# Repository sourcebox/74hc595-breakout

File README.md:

# About

KiCad project files of a breakout board containing 8 cascaded 74HC595
shift registers offering serial-in/parallel-out functionality.

This board is intended as microcontroller GPIO extension for prototyping purposes.

# License

CC-BY-4.0

By: Oliver Rockstedt <info@sourcebox.de>

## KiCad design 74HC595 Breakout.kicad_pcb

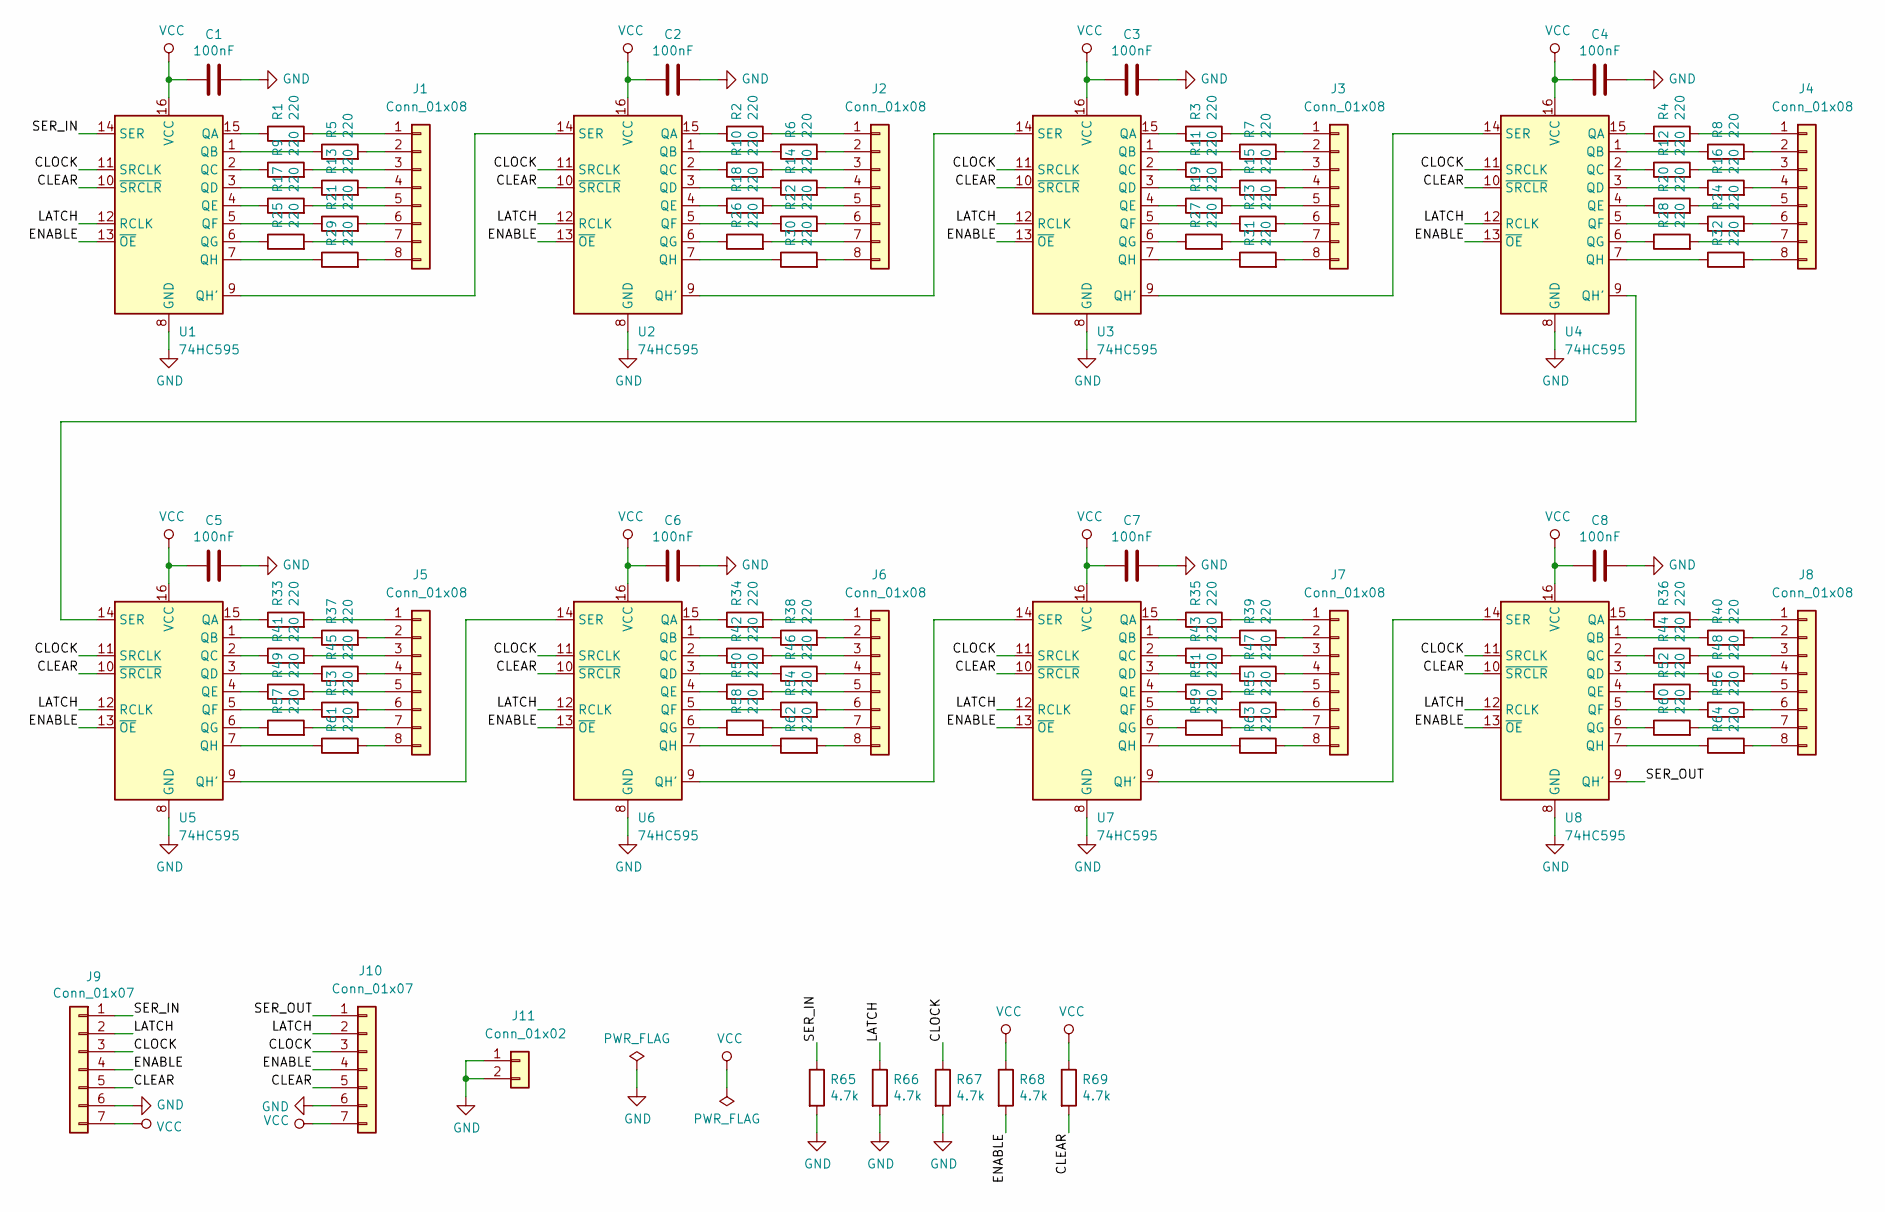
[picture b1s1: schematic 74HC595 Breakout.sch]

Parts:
C1, C2, C3, C4, C5, C6, C7, C8: 100nF; C_0805_2012Metric
J1, J2, J3, J4, J5, J6, J7, J8: Conn_01x08; PinHeader_1x08_P2.54mm_Vertical
J9, J10: Conn_01x07; PinHeader_1x07_P2.54mm_Vertical
J11: Conn_01x02; PinHeader_1x02_P2.54mm_Vertical
R1, R2, R3, R4, R5, R6, R7, R8, R9, R10, R11, R12, R13, R14, R15, R16, R17, R18, R19, R20, R21, R22, R23, R24, R25, R26, R27, R28, R29, R30, R31, R32, R33, R34, R35, R36, R37, R38, R39, R40, R41, R42, R43, R44, R45, R46, R47, R48, R49, R50, R51, R52, R53, R54, R55, R56, R57, R58, R59, R60, R61, R62, R63, R64: 220; R_0805_2012Metric
R65, R66, R67, R68, R69: 4.7k; R_0805_2012Metric
U1, U2, U3, U4, U5, U6, U7, U8: 74HC595; SOIC-16_3.9x9.9mm_P1.27mm

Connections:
/CLEAR: J9.5, J10.5, R69.2, U1.10 (~SRCLR), U2.10 (~SRCLR), U3.10 (~SRCLR), U4.10 (~SRCLR), U5.10 (~SRCLR), U6.10 (~SRCLR), U7.10 (~SRCLR), U8.10 (~SRCLR)
/CLOCK: J9.3, J10.3, R67.1, U1.11 (SRCLK), U2.11 (SRCLK), U3.11 (SRCLK), U4.11 (SRCLK), U5.11 (SRCLK), U6.11 (SRCLK), U7.11 (SRCLK), U8.11 (SRCLK)
/ENABLE: J9.4, J10.4, R68.2, U1.13 (~OE), U2.13 (~OE), U3.13 (~OE), U4.13 (~OE), U5.13 (~OE), U6.13 (~OE), U7.13 (~OE), U8.13 (~OE)
/LATCH: J9.2, J10.2, R66.1, U1.12 (RCLK), U2.12 (RCLK), U3.12 (RCLK), U4.12 (RCLK), U5.12 (RCLK), U6.12 (RCLK), U7.12 (RCLK), U8.12 (RCLK)
/SER_IN: J9.1, R65.1, U1.14 (SER)
/SER_OUT: J10.1, U8.9 (QH')
GND: C1.1, C2.1, C3.1, C4.1, C5.1, C6.1, C7.1, C8.1, J9.6, J10.6, J11.1, J11.2, R65.2, R66.2, R67.2, U1.8 (GND), U2.8 (GND), U3.8 (GND), U4.8 (GND), U5.8 (GND), U6.8 (GND), U7.8 (GND), U8.8 (GND)
unnamed: J1.1, R1.2
unnamed: J1.2, R5.2
unnamed: J1.3, R9.2
unnamed: J1.4, R13.2
unnamed: J1.5, R17.2
unnamed: J1.6, R21.2
unnamed: J1.7, R25.2
unnamed: J1.8, R29.2
unnamed: J2.1, R2.2
unnamed: J2.2, R6.2
unnamed: J2.3, R10.2
unnamed: J2.4, R14.2
unnamed: J2.5, R18.2
unnamed: J2.6, R22.2
unnamed: J2.7, R26.2
unnamed: J2.8, R30.2
unnamed: J3.1, R3.2
unnamed: J3.2, R7.2
unnamed: J3.3, R11.2
unnamed: J3.4, R15.2
unnamed: J3.5, R19.2
unnamed: J3.6, R23.2
unnamed: J3.7, R27.2
unnamed: J3.8, R31.2
unnamed: J4.1, R4.2
unnamed: J4.2, R8.2
unnamed: J4.3, R12.2
unnamed: J4.4, R16.2
unnamed: J4.5, R20.2
unnamed: J4.6, R24.2
unnamed: J4.7, R28.2
unnamed: J4.8, R32.2
unnamed: J5.1, R33.2
unnamed: J5.2, R37.2
unnamed: J5.3, R41.2
unnamed: J5.4, R45.2
unnamed: J5.5, R49.2
unnamed: J5.6, R53.2
unnamed: J5.7, R57.2
unnamed: J5.8, R61.2
unnamed: J6.1, R34.2
unnamed: J6.2, R38.2
unnamed: J6.3, R42.2
unnamed: J6.4, R46.2
unnamed: J6.5, R50.2
unnamed: J6.6, R54.2
unnamed: J6.7, R58.2
unnamed: J6.8, R62.2
unnamed: J7.1, R35.2
unnamed: J7.2, R39.2
unnamed: J7.3, R43.2
unnamed: J7.4, R47.2
unnamed: J7.5, R51.2
unnamed: J7.6, R55.2
unnamed: J7.7, R59.2
unnamed: J7.8, R63.2
unnamed: J8.1, R36.2
unnamed: J8.2, R40.2
unnamed: J8.3, R44.2
unnamed: J8.4, R48.2
unnamed: J8.5, R52.2
unnamed: J8.6, R56.2
unnamed: J8.7, R60.2
unnamed: J8.8, R64.2
unnamed: R1.1, U1.15 (QA)
unnamed: R2.1, U2.15 (QA)
unnamed: R3.1, U3.15 (QA)
unnamed: R4.1, U4.15 (QA)
unnamed: R5.1, U1.1 (QB)
unnamed: R6.1, U2.1 (QB)
unnamed: R7.1, U3.1 (QB)
unnamed: R8.1, U4.1 (QB)
unnamed: R9.1, U1.2 (QC)
unnamed: R10.1, U2.2 (QC)
unnamed: R11.1, U3.2 (QC)
unnamed: R12.1, U4.2 (QC)
unnamed: R13.1, U1.3 (QD)
unnamed: R14.1, U2.3 (QD)
unnamed: R15.1, U3.3 (QD)
unnamed: R16.1, U4.3 (QD)
unnamed: R17.1, U1.4 (QE)
unnamed: R18.1, U2.4 (QE)
unnamed: R19.1, U3.4 (QE)
unnamed: R20.1, U4.4 (QE)
unnamed: R21.1, U1.5 (QF)
unnamed: R22.1, U2.5 (QF)
unnamed: R23.1, U3.5 (QF)
unnamed: R24.1, U4.5 (QF)
unnamed: R25.1, U1.6 (QG)
unnamed: R26.1, U2.6 (QG)
unnamed: R27.1, U3.6 (QG)
unnamed: R28.1, U4.6 (QG)
unnamed: R29.1, U1.7 (QH)
unnamed: R30.1, U2.7 (QH)
unnamed: R31.1, U3.7 (QH)
unnamed: R32.1, U4.7 (QH)
unnamed: R33.1, U5.15 (QA)
unnamed: R34.1, U6.15 (QA)
unnamed: R35.1, U7.15 (QA)
unnamed: R36.1, U8.15 (QA)
unnamed: R37.1, U5.1 (QB)
unnamed: R38.1, U6.1 (QB)
unnamed: R39.1, U7.1 (QB)
unnamed: R40.1, U8.1 (QB)
unnamed: R41.1, U5.2 (QC)
unnamed: R42.1, U6.2 (QC)
unnamed: R43.1, U7.2 (QC)
unnamed: R44.1, U8.2 (QC)
unnamed: R45.1, U5.3 (QD)
unnamed: R46.1, U6.3 (QD)
unnamed: R47.1, U7.3 (QD)
unnamed: R48.1, U8.3 (QD)
unnamed: R49.1, U5.4 (QE)
unnamed: R50.1, U6.4 (QE)
unnamed: R51.1, U7.4 (QE)
unnamed: R52.1, U8.4 (QE)
unnamed: R53.1, U5.5 (QF)
unnamed: R54.1, U6.5 (QF)
unnamed: R55.1, U7.5 (QF)
unnamed: R56.1, U8.5 (QF)
unnamed: R57.1, U5.6 (QG)
unnamed: R58.1, U6.6 (QG)
unnamed: R59.1, U7.6 (QG)
unnamed: R60.1, U8.6 (QG)
unnamed: R61.1, U5.7 (QH)
unnamed: R62.1, U6.7 (QH)
unnamed: R63.1, U7.7 (QH)
unnamed: R64.1, U8.7 (QH)
unnamed: U1.9 (QH'), U2.14 (SER)
unnamed: U2.9 (QH'), U3.14 (SER)
unnamed: U3.9 (QH'), U4.14 (SER)
unnamed: U4.9 (QH'), U5.14 (SER)
unnamed: U5.9 (QH'), U6.14 (SER)
unnamed: U6.9 (QH'), U7.14 (SER)
unnamed: U7.9 (QH'), U8.14 (SER)
VCC: C1.2, C2.2, C3.2, C4.2, C5.2, C6.2, C7.2, C8.2, J9.7, J10.7, R68.1, R69.1, U1.16 (VCC), U2.16 (VCC), U3.16 (VCC), U4.16 (VCC), U5.16 (VCC), U6.16 (VCC), U7.16 (VCC), U8.16 (VCC)

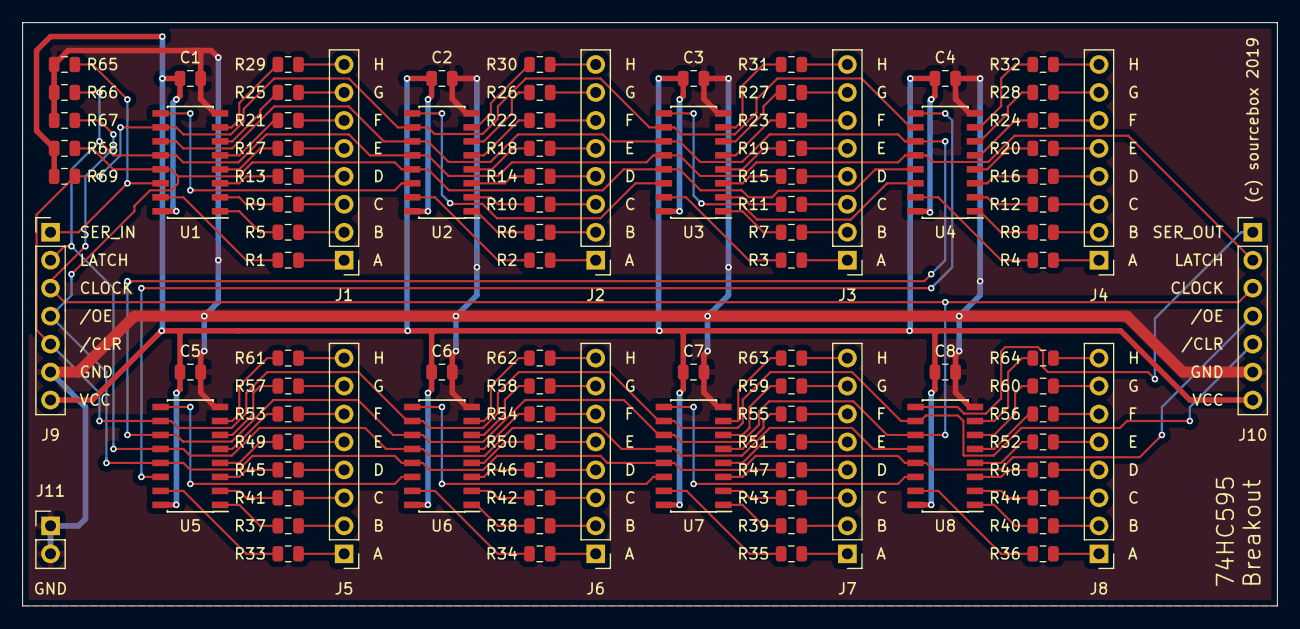
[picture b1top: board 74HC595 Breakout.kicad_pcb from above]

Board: 2 copper layers, 114.0 x 53.0 mm, 96 parts (0 on the bottom side), 143 nets.

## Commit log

2019-03-26 Initial import
2019-03-26 Ground planes
2019-03-26 Board dimensions added
2019-04-09 Gerbers export
2021-03-04 License and readme
2021-12-26 PDF export
